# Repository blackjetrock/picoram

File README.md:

# picoram
SPI RAM expansion card for Pico

PCB that sits on top of a PIco and allows an SPI RAM to be soldered to it and acessed by the Pico.

Code to drive this is not here. I have some SPI RAM access functions in the picoputer code.

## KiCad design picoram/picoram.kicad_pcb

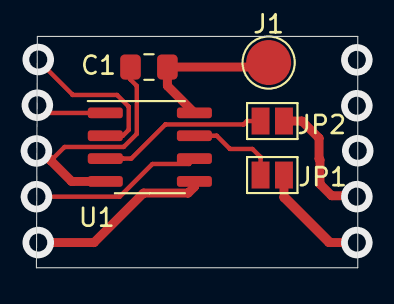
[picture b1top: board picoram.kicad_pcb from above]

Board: 2 copper layers, 17.8 x 12.8 mm, 5 parts (0 on the bottom side), 4 nets.

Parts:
C1: C_Small; C_0805_2012Metric_Pad1.15x1.40mm_HandSolder
J1: Conn_01x01_Female; TestPoint_Pad_D2.5mm
JP1, JP2: Jumper_NO_Small; SolderJumper-2_P1.3mm_Open_Pad1.0x1.5mm
U1: ESP-PSRAM32; SOIC-8_3.9x4.9mm_P1.27mm

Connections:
unnamed: C1.1, J1.1, U1.8
unnamed: C1.2, U1.4
unnamed: JP1.1, U1.7
unnamed: JP2.1, U1.3

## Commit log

2021-08-12 Initail check in
